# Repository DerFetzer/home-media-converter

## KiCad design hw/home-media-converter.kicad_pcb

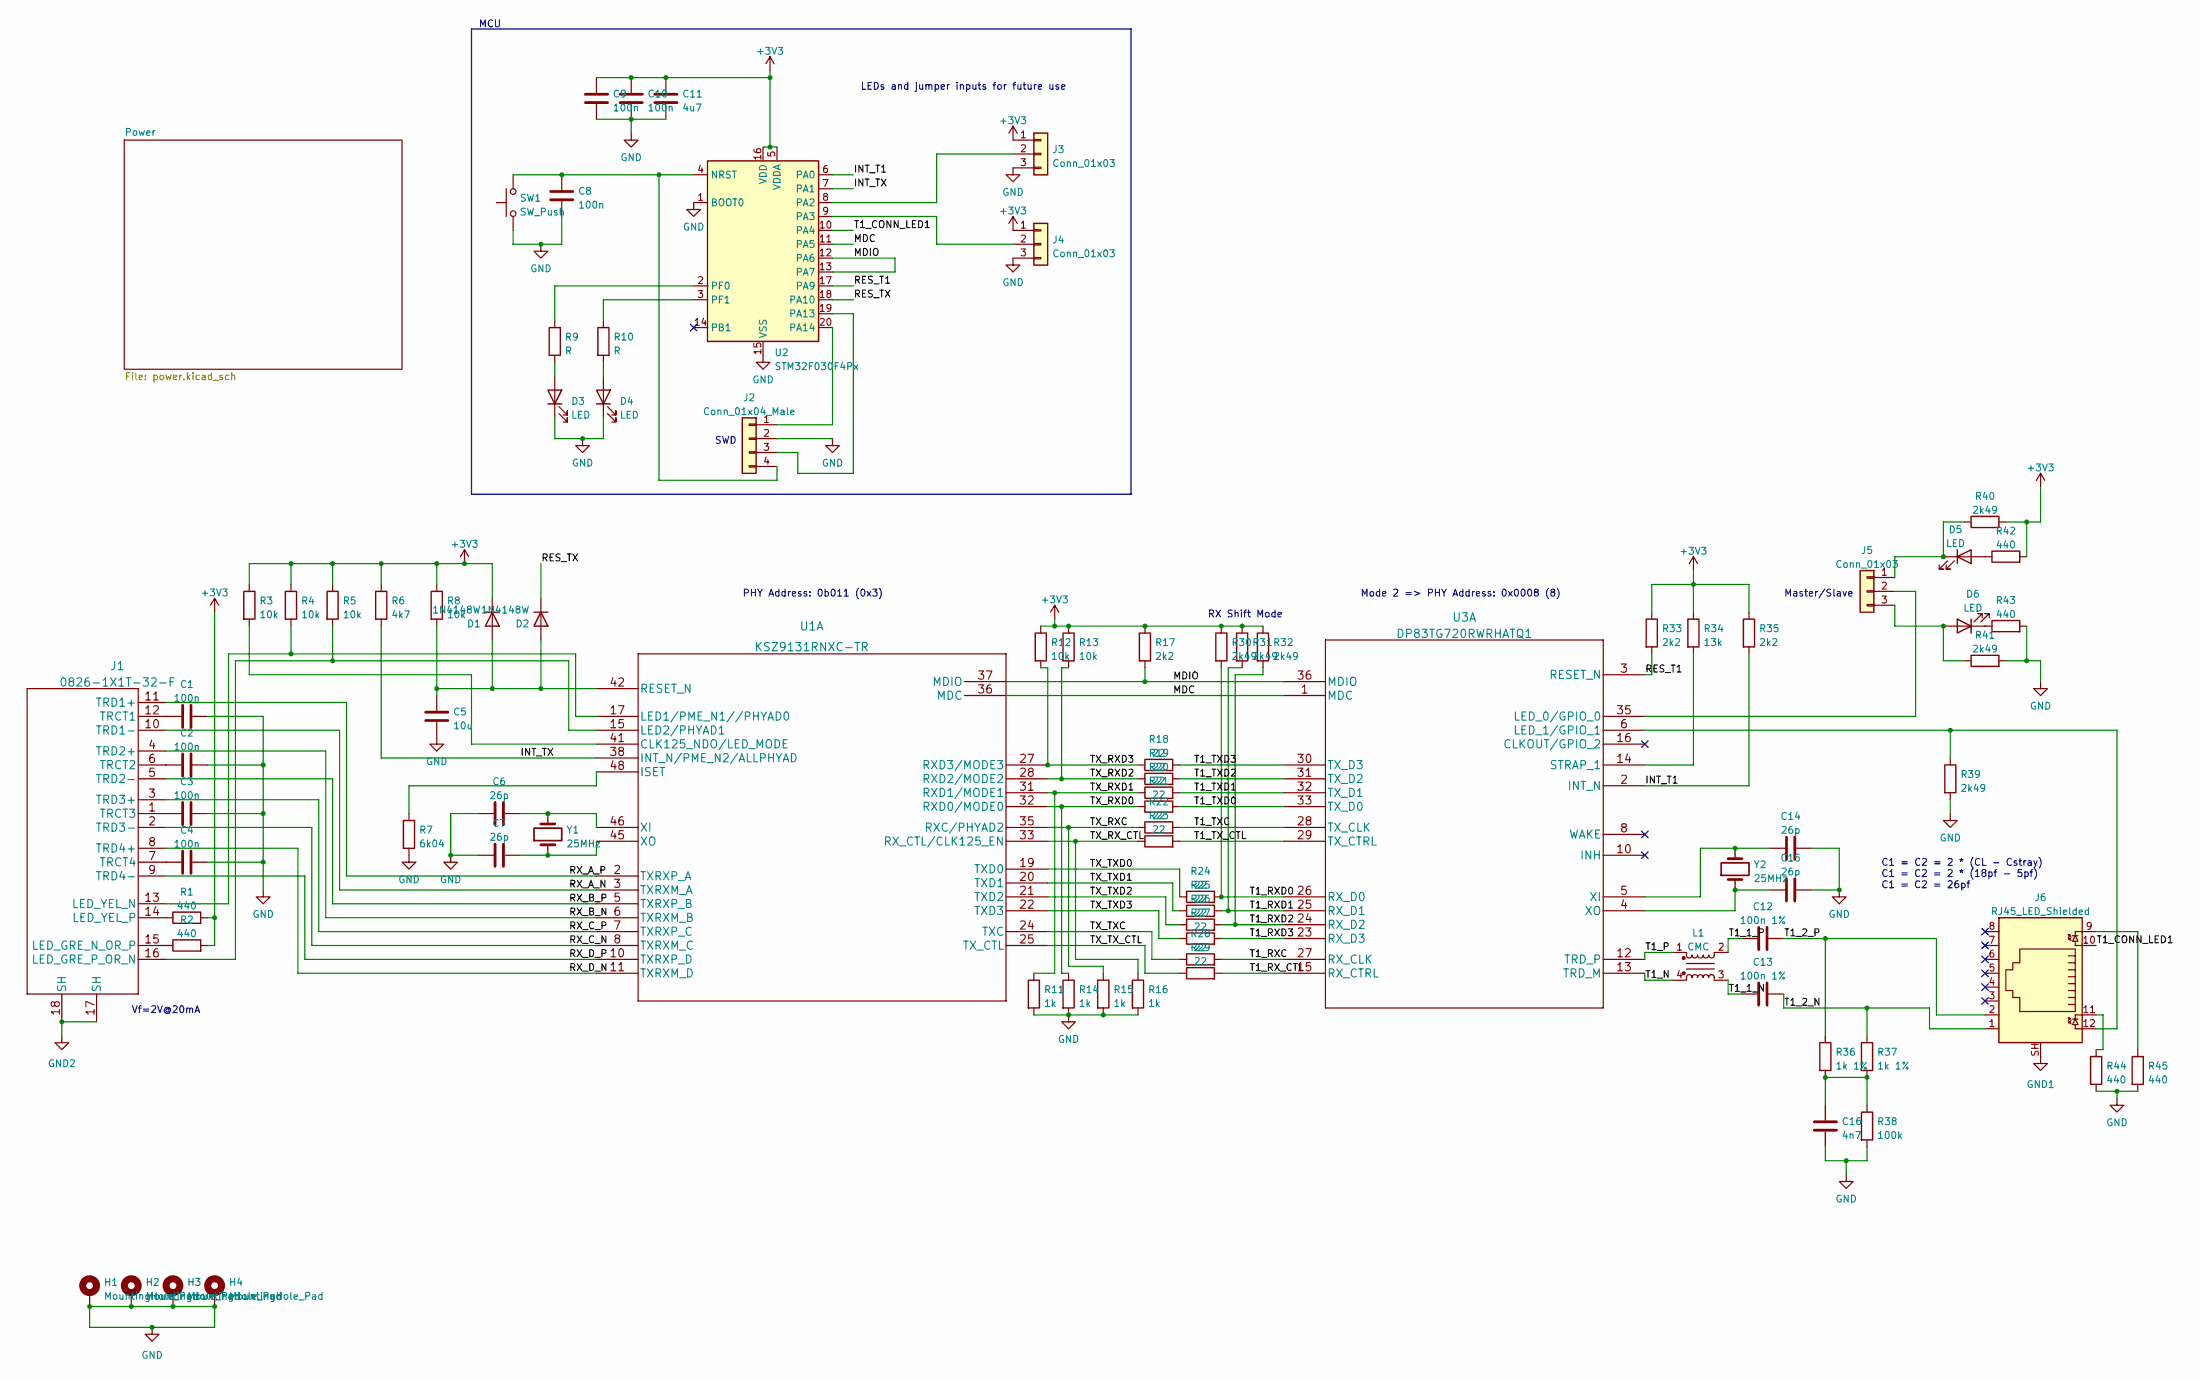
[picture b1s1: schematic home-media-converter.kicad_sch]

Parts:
C1, C2, C3, C4, C8, C9, C10: 100n; C_0402_1005Metric
C5: 10u; C_0402_1005Metric
C6, C7, C14, C15: 26p; C_0402_1005Metric
C11: 4u7; C_0402_1005Metric
C12, C13: 100n 1%; C_0402_1005Metric
C16: 4n7; C_1206_3216Metric
D1, D2: 1N4148W; D_SOD-123
D3, D4, D5, D6: LED; LED_0603_1608Metric
H1, H2, H3, H4: MountingHole_Pad; MountingHole_2.2mm_M2_DIN965_Pad_TopBottom
J1: 0826-1X1T-32-F
J2: Conn_01x04_Male; PinHeader_1x04_P2.54mm_Vertical
J3, J4, J5: Conn_01x03; PinHeader_1x03_P2.54mm_Vertical
J6: RJ45_LED_Shielded; RJ45_Amphenol_RJHSE538X
L1: CMC; DLW32MH101XK2L
R1, R2, R42, R43, R44, R45: 440; R_0402_1005Metric
R3, R4, R5, R8, R12, R13: 10k; R_0402_1005Metric
R6: 4k7; R_0402_1005Metric
R7: 6k04; R_0402_1005Metric
R9, R10: R; R_0402_1005Metric
R11, R14, R15, R16: 1k; R_0402_1005Metric
R17, R33, R35: 2k2; R_0402_1005Metric
R18, R19, R20, R21, R22, R23, R24, R25, R26, R27, R28, R29: 22; R_0402_1005Metric
R30, R31, R32, R39, R40, R41: 2k49; R_0402_1005Metric
R34: 13k; R_0402_1005Metric
R36, R37: 1k 1%; R_1206_3216Metric
R38: 100k; R_0805_2012Metric
SW1: SW_Push; SW_Push_1P1T_NO_CK_KMR2
U1: KSZ9131RNXC-TR
U2: STM32F030F4Px; TSSOP-20_4.4x6.5mm_P0.65mm
U3: DP83TG720RWRHATQ1
Y1, Y2: 25MHz; Crystal_SMD_5032-2Pin_5.0x3.2mm

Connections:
+3V3: C9.1, C10.1, C11.1, D1.1 (K), J3.1, J4.1, R1.2, R2.2, R3.1, R4.1, R5.1, R6.1, R8.1, R12.1, R13.1, R17.1, R30.1, R31.1, R32.1, R33.1, R34.1, R35.1, R40.2, R42.2, U2.5 (VDDA), U2.16 (VDD); also elsewhere on the board
/INT_T1: R35.2, U2.6 (PA0), U3.2 (INT_N)
/INT_TX: R6.2, U1.38 (INT_N/PME_N2/ALLPHYAD), U2.7 (PA1)
/MDC: U1.36 (MDC), U2.11 (PA5), U3.1 (MDC)
/MDIO: R17.2, U1.37 (MDIO), U2.12 (PA6), U2.13 (PA7), U3.36 (MDIO)
/RES_T1: R33.2, U2.17 (PA9), U3.3 (RESET_N)
/RES_TX: D2.1 (K), U2.18 (PA10)
/RX_A_N: J1.10 (TRD1-), U1.3 (TXRXM_A); also elsewhere on the board
/RX_A_P: J1.11 (TRD1+), U1.2 (TXRXP_A); also elsewhere on the board
/RX_B_N: J1.4 (TRD2+), U1.6 (TXRXM_B); also elsewhere on the board
/RX_B_P: J1.5 (TRD2-), U1.5 (TXRXP_B); also elsewhere on the board
/RX_C_N: J1.2 (TRD3-), U1.8 (TXRXM_C); also elsewhere on the board
/RX_C_P: J1.3 (TRD3+), U1.7 (TXRXP_C); also elsewhere on the board
/RX_D_N: J1.8 (TRD4+), U1.11 (TXRXM_D); also elsewhere on the board
/RX_D_P: J1.9 (TRD4-), U1.10 (TXRXP_D); also elsewhere on the board
/T1_1_N: C13.1, L1.3
/T1_1_P: C12.1, L1.2
/T1_2_N: C13.2, J6.1, R37.1
/T1_2_P: C12.2, J6.2, R36.1
/T1_CONN_LED1: J6.10, U2.10 (PA4)
/T1_N: L1.4, U3.13 (TRD_M)
/T1_P: L1.1, U3.12 (TRD_P)
/T1_RXC: R28.2, U3.27 (RX_CLK)
/T1_RXD0: R24.2, R30.2, U3.26 (RX_D0)
/T1_RXD1: R25.2, R31.2, U3.25 (RX_D1)
/T1_RXD2: R26.2, R32.2, U3.24 (RX_D2)
/T1_RXD3: R27.2, U3.23 (RX_D3)
/T1_RX_CTL: R29.2, U3.15 (RX_CTRL)
/T1_TXC: R22.2, U3.28 (TX_CLK)
/T1_TXD0: R21.2, U3.33 (TX_D0)
/T1_TXD1: R20.2, U3.32 (TX_D1)
/T1_TXD2: R19.2, U3.31 (TX_D2)
/T1_TXD3: R18.2, U3.30 (TX_D3)
/T1_TX_CTL: R23.2, U3.29 (TX_CTRL)
/TX_RXC: R15.1, R22.1, U1.35 (RXC/PHYAD2)
/TX_RXD0: R14.1, R21.1, U1.32 (RXD0/MODE0)
/TX_RXD1: R11.1, R20.1, U1.31 (RXD1/MODE1)
/TX_RXD2: R13.2, R19.1, U1.28 (RXD2/MODE2)
/TX_RXD3: R12.2, R18.1, U1.27 (RXD3/MODE3)
/TX_RX_CTL: R16.1, R23.1, U1.33 (RX_CTL/CLK125_EN)
/TX_TXC: R28.1, U1.24 (TXC)
/TX_TXD0: R24.1, U1.19 (TXD0)
/TX_TXD1: R25.1, U1.20 (TXD1)
/TX_TXD2: R26.1, U1.21 (TXD2)
/TX_TXD3: R27.1, U1.22 (TXD3)
/TX_TX_CTL: R29.1, U1.25 (TX_CTL)
GND: C1.2, C2.2, C3.2, C4.2, C5.2, C6.1, C7.1, C8.2, C9.2, C10.2, C11.2, C14.2, C15.2, C16.2, D3.1 (K), D4.1 (K), H1.1, H2.1, H3.1, H4.1, J2.2, J3.3, J4.3, R7.2, R11.2, R14.2, R15.2, R16.2, R38.2, R39.2, R41.2, R43.2, R44.2, R45.2, SW1.1, U2.1 (BOOT0), U2.15 (VSS); also elsewhere on the board
GND1: J6.SH
unnamed: C16.1, R36.2, R37.2, R38.1
unnamed: C5.1, D1.2 (A), D2.2 (A), R8.2, U1.42 (RESET_N)
unnamed: D3.2 (A), R9.2
unnamed: D4.2 (A), R10.2
unnamed: D5.2 (A), R42.1
unnamed: D5.1 (K), J5.1, R40.1
unnamed: D6.2 (A), J5.3, R41.1
unnamed: D6.1 (K), R43.1
unnamed 66: J1.15 (LED_GRE_N_OR_P), R2.1; also elsewhere on the board
unnamed 67: J1.16 (LED_GRE_P_OR_N), R5.2, U1.15 (LED2/PHYAD1); also elsewhere on the board
unnamed 68: J1.13 (LED_YEL_N), R4.2, U1.17 (LED1/PME_N1//PHYAD0); also elsewhere on the board
unnamed 69: J1.14 (LED_YEL_P), R1.1; also elsewhere on the board
unnamed: J1.17 (SH), J1.18 (SH)
unnamed 71: C1.1, J1.12 (TRCT1); also elsewhere on the board
unnamed 72: C2.1, J1.6 (TRCT2); also elsewhere on the board
unnamed 73: C3.1, J1.1 (TRCT3); also elsewhere on the board
unnamed 74: C4.1, J1.7 (TRCT4); also elsewhere on the board
unnamed: J2.1, U2.20 (PA14)
unnamed: J2.3, U2.19 (PA13)
unnamed: C8.1, J2.4, SW1.2, U2.4 (NRST)
unnamed: J3.2, U2.8 (PA2)
unnamed: J4.2, U2.9 (PA3)
unnamed: J5.2, U3.35 (LED_0/GPIO_0)
unnamed: J6.9, R45.1
unnamed: J6.11, R44.1
unnamed: R3.2, U1.41 (CLK125_NDO/LED_MODE)
unnamed: R7.1, U1.48 (ISET)
unnamed: C6.2, U1.46 (XI), Y1.2
unnamed: C7.2, U1.45 (XO), Y1.1
unnamed: R9.1, U2.2 (PF0)
unnamed: R10.1, U2.3 (PF1)
unnamed: J6.12, R39.1, U3.6 (LED_1/GPIO_1)
unnamed: R34.2, U3.14 (STRAP_1)
unnamed: C14.1, U3.5 (XI), Y2.2
unnamed: C15.1, U3.4 (XO), Y2.1

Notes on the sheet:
Vf=2V@20mA
LEDs and jumper inputs for future use
Mode 2 => PHY Address: 0x0008 (8)
C1 = C2 = 2 * (CL - Cstray) C1 = C2 = 2 * (18pf - 5pf) C1 = C2 = 26pf
SWD
RX Shift Mode
PHY Address: 0b011 (0x3)
MCU
Master/Slave

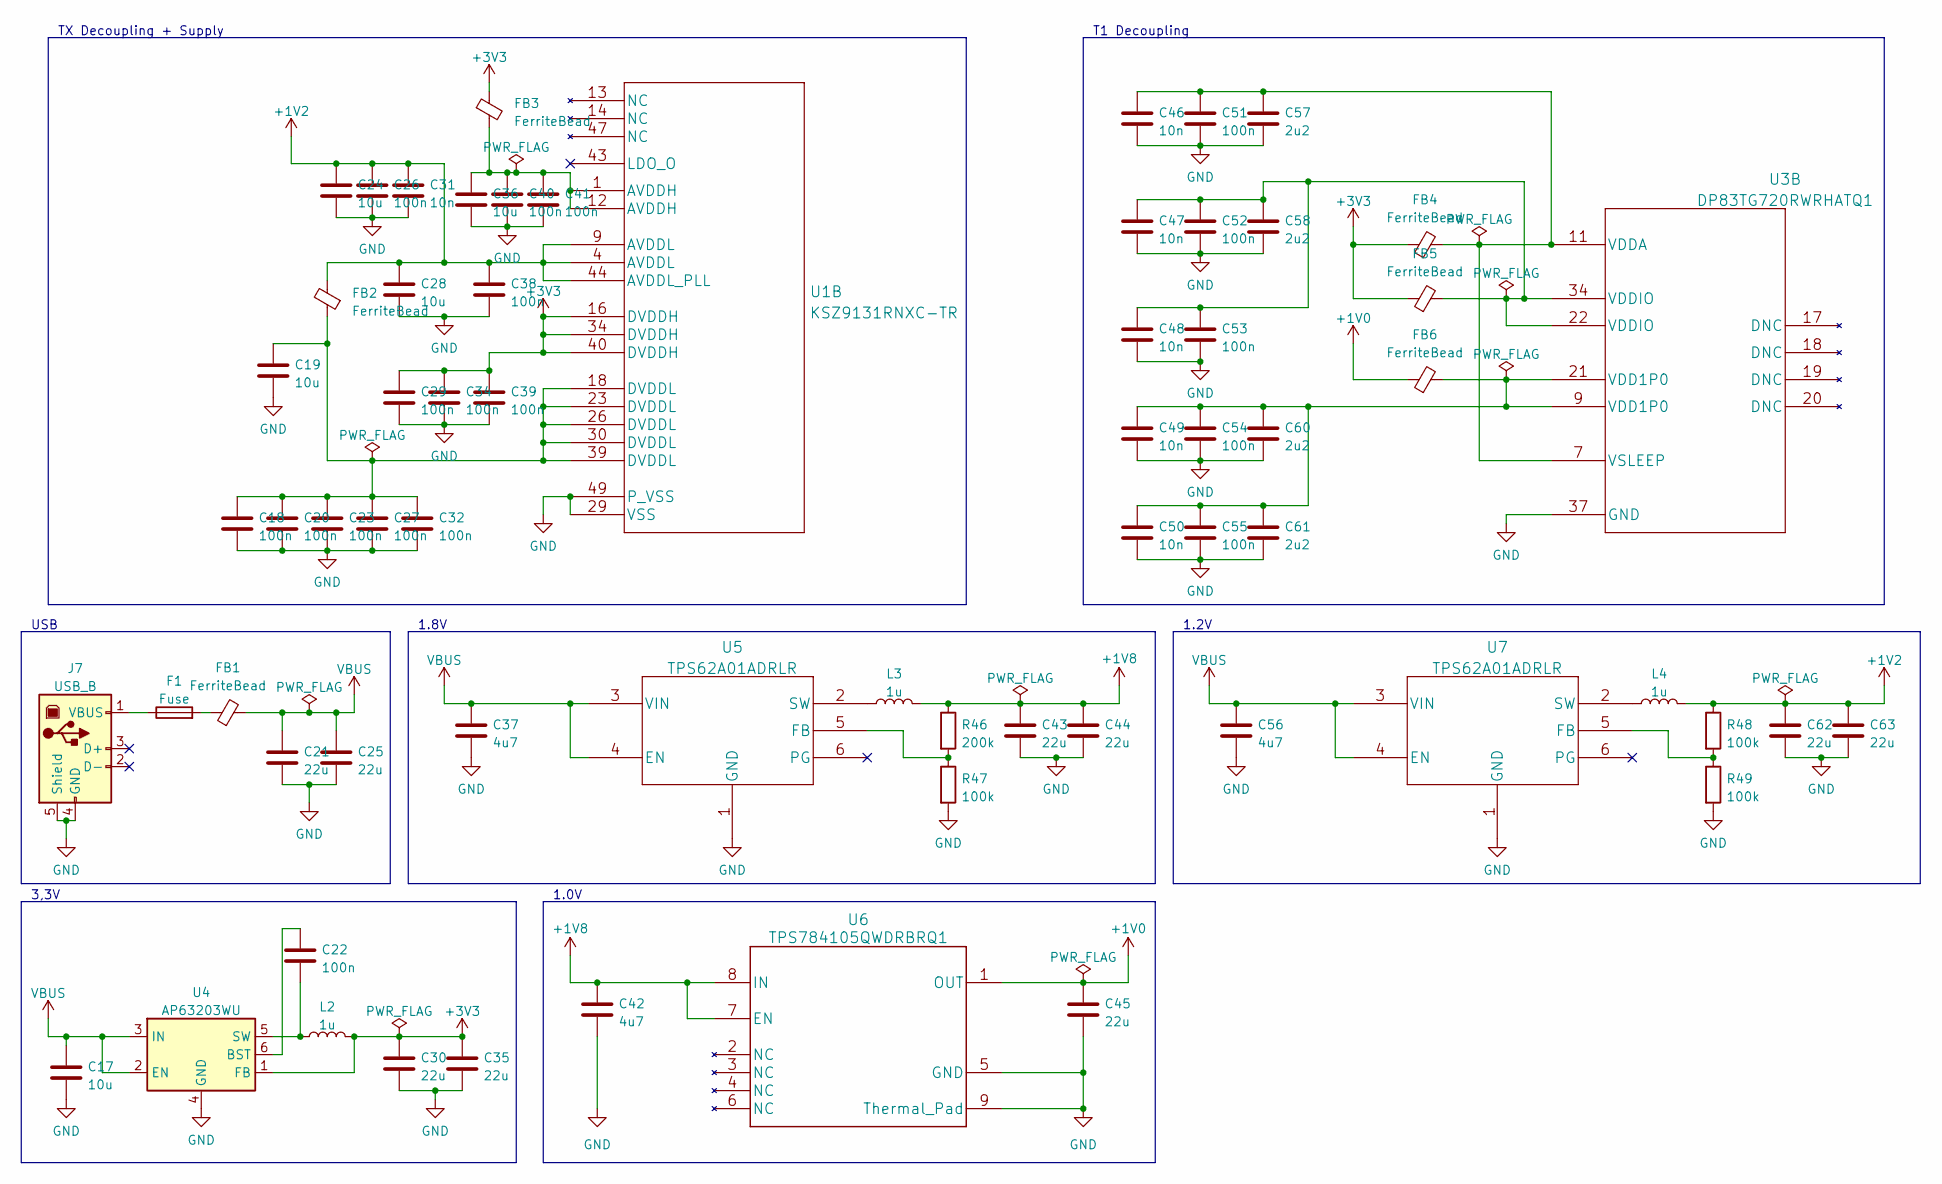
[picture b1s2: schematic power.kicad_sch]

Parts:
C17, C19, C24, C28, C36: 10u; C_0402_1005Metric
C18, C20, C22, C23, C26, C27, C29, C32, C34, C38, C39, C40, C41, C51, C52, C53, C54, C55: 100n; C_0402_1005Metric
C21, C25, C30, C35, C43, C44, C45, C62, C63: 22u; C_0603_1608Metric
C31, C46, C47, C48, C49, C50: 10n; C_0402_1005Metric
C37, C42, C56: 4u7; C_0402_1005Metric
C57, C58, C60, C61: 2u2; C_0402_1005Metric
F1: Fuse; Fuse_0603_1608Metric
FB1, FB2, FB3, FB4, FB5, FB6: FerriteBead; L_0603_1608Metric
J7: USB_B; USB_Micro-B_Wuerth_629105150521
L2, L3, L4: 1u; L_1008_2520Metric
R46: 200k; R_0402_1005Metric
R47, R48, R49: 100k; R_0402_1005Metric
U1: KSZ9131RNXC-TR
U3: DP83TG720RWRHATQ1
U4: AP63203WU; TSOT-23-6
U5, U7: TPS62A01ADRLR
U6: TPS784105QWDRBRQ1

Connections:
+1V0: C45.1, FB6.1, U6.1 (OUT)
+1V2: C24.1, C26.1, C28.1, C31.1, C38.1, C62.1, C63.1, FB2.2, L4.2, R48.1, U1.4 (AVDDL), U1.9 (AVDDL), U1.44 (AVDDL_PLL)
+1V8: C42.1, C43.1, C44.1, L3.2, R46.1, U6.7 (EN), U6.8 (IN)
+3V3: C29.1, C30.1, C34.1, C35.1, C39.1, FB3.1, FB4.1, FB5.1, L2.2, U1.16 (DVDDH), U1.34 (DVDDH), U1.40 (DVDDH), U4.1 (FB); also elsewhere on the board
GND: C17.2, C18.2, C19.2, C20.2, C21.2, C23.2, C24.2, C25.2, C26.2, C27.2, C28.2, C29.2, C30.2, C31.2, C32.2, C34.2, C35.2, C36.2, C37.2, C38.2, C39.2, C40.2, C41.2, C42.2, C43.2, C44.2, C45.2, C46.2, C47.2, C48.2, C49.2, C50.2, C51.2, C52.2, C53.2, C54.2, C55.2, C56.2, C57.2, C58.2, C60.2, C61.2, C62.2, C63.2, J7.4 (GND), J7.5 (Shield), R47.2, R49.2, U1.29 (VSS), U1.49 (P_VSS), U3.37 (GND), U4.4 (GND), U5.1 (GND), U6.5 (GND), U6.9 (Thermal_Pad), U7.1 (GND); also elsewhere on the board
unnamed: C18.1, C19.1, C20.1, C23.1, C27.1, C32.1, FB2.1, U1.18 (DVDDL), U1.23 (DVDDL), U1.26 (DVDDL), U1.30 (DVDDL), U1.39 (DVDDL)
unnamed: C36.1, C40.1, C41.1, FB3.2, U1.1 (AVDDH), U1.12 (AVDDH)
unnamed: C46.1, C51.1, C57.1, FB4.2, U3.7 (VSLEEP), U3.11 (VDDA)
unnamed: C47.1, C48.1, C52.1, C53.1, C58.1, FB5.2, U3.22 (VDDIO), U3.34 (VDDIO)
unnamed: C49.1, C50.1, C54.1, C55.1, C60.1, C61.1, FB6.2, U3.9 (VDD1P0), U3.21 (VDD1P0)
unnamed: F1.2, FB1.1
unnamed: F1.1, J7.1 (VBUS)
unnamed: C22.1, U4.6 (BST)
unnamed: C22.2, L2.1, U4.5 (SW)
unnamed: R46.2, R47.1, U5.5 (FB)
unnamed: L3.1, U5.2 (SW)
unnamed: R48.2, R49.1, U7.5 (FB)
unnamed: L4.1, U7.2 (SW)
VBUS: C17.1, C21.1, C25.1, C37.1, C56.1, FB1.2, U4.2 (EN), U4.3 (IN), U5.3 (VIN), U5.4 (EN), U7.3 (VIN), U7.4 (EN)

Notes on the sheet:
USB
TX Decoupling + Supply
1.0V
1.2V
3,3V
1.8V
T1 Decoupling

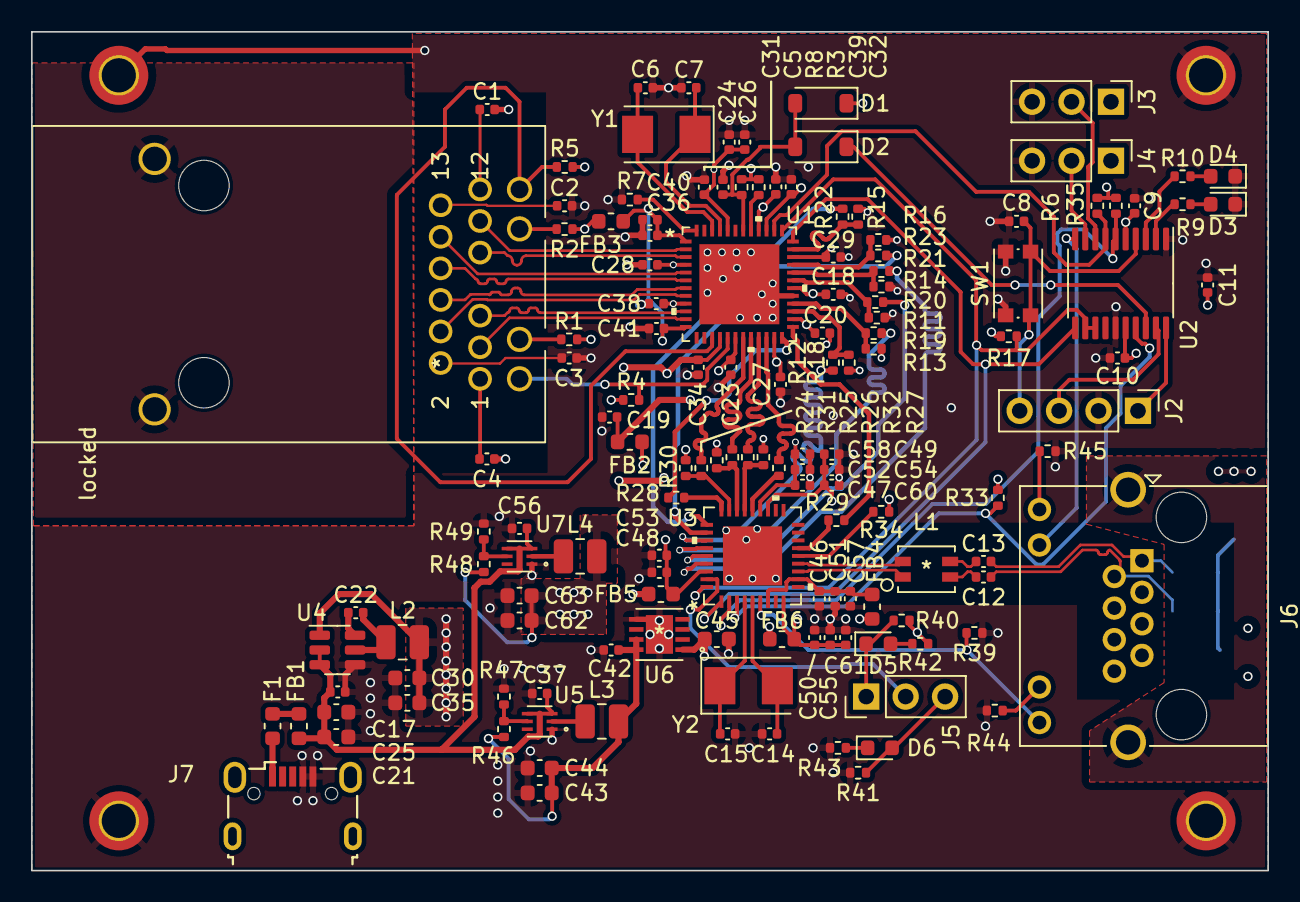
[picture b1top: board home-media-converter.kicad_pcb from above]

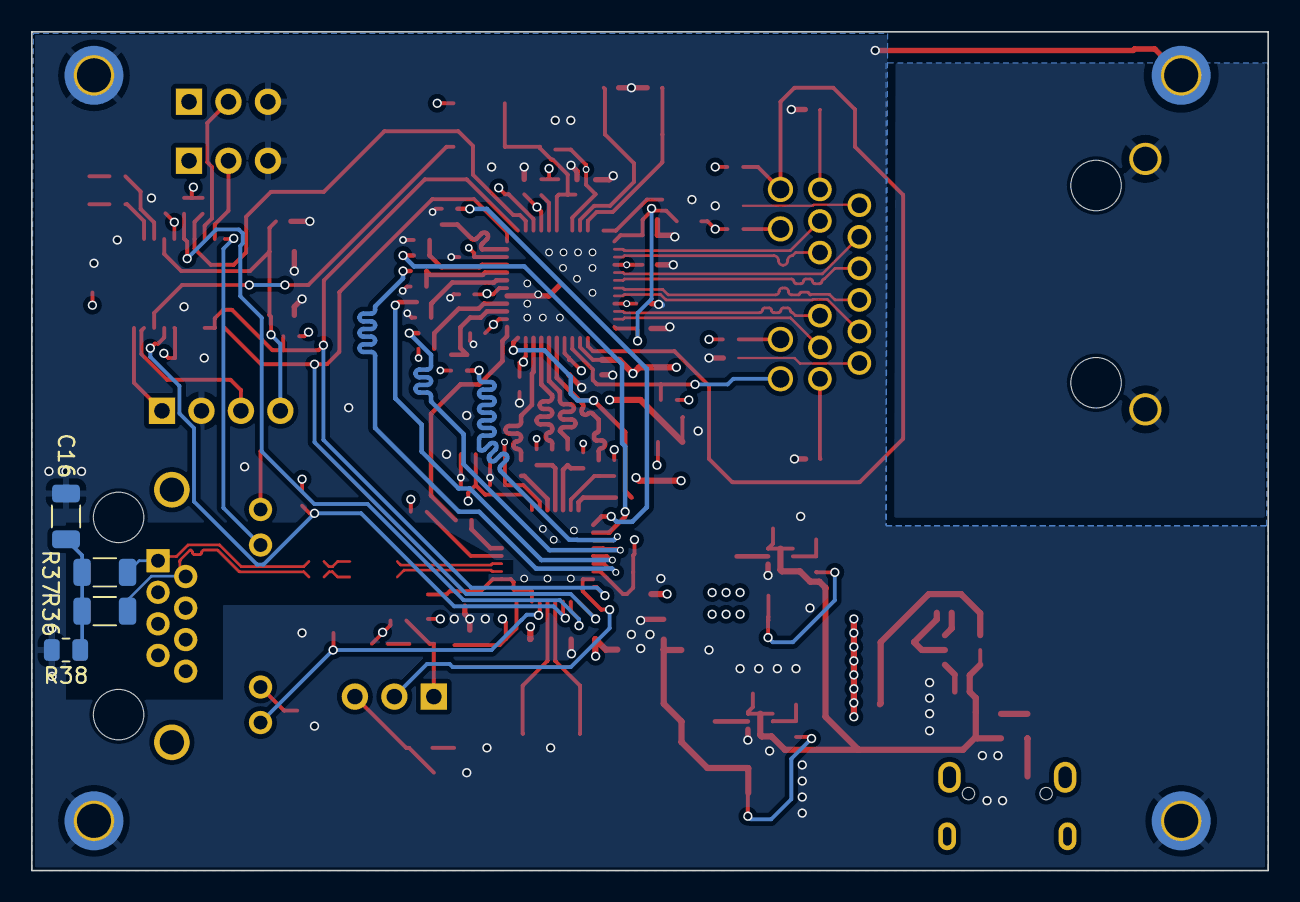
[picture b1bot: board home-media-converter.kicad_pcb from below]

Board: 4 copper layers, 79.6 x 54.0 mm, 148 parts (4 on the bottom side), 99 nets.

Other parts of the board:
locked: 0826-1X1T-32-F

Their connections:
/RX_A_N: locked.10 (TRD1-); also elsewhere on the board
/RX_A_P: locked.11 (TRD1+); also elsewhere on the board
/RX_B_N: locked.4 (TRD2+); also elsewhere on the board
/RX_B_P: locked.5 (TRD2-); also elsewhere on the board
/RX_C_N: locked.2 (TRD3-); also elsewhere on the board
/RX_C_P: locked.3 (TRD3+); also elsewhere on the board
/RX_D_N: locked.8 (TRD4+); also elsewhere on the board
/RX_D_P: locked.9 (TRD4-); also elsewhere on the board
GND2: locked.17 (SH), locked.18 (SH)
unnamed 66: locked.15 (LED_GRE_N_OR_P); also elsewhere on the board
unnamed 67: locked.16 (LED_GRE_P_OR_N); also elsewhere on the board
unnamed 68: locked.13 (LED_YEL_N); also elsewhere on the board
unnamed 69: locked.14 (LED_YEL_P); also elsewhere on the board
unnamed 71: locked.12 (TRCT1); also elsewhere on the board
unnamed 72: locked.6 (TRCT2); also elsewhere on the board
unnamed 73: locked.1 (TRCT3); also elsewhere on the board
unnamed 74: locked.7 (TRCT4); also elsewhere on the board

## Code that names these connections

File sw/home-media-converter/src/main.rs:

#![no_main]
#![no_std]

use home_media_converter as _;
use stm32f0xx_hal::pac::Peripherals; // global logger + panicking-behavior + memory layout
use stm32f0xx_hal::prelude::*;

use home_media_converter::smi::{Smi, T1Registers};

#[cortex_m_rt::entry]
fn main() -> ! {
    defmt::println!("Hello, world!");
    let mut dp = Peripherals::take().unwrap();
    let mut rcc = dp.RCC.configure().sysclk(8.mhz()).freeze(&mut dp.FLASH);

    let gpioa = dp.GPIOA.split(&mut rcc);
    let gpiof = dp.GPIOF.split(&mut rcc);

    let (jumper3, mut led_t1_conn, mdc, mdio) = cortex_m::interrupt::free(move |cs| {
        let _int_t1 = gpioa.pa0;
        let _int_tx = gpioa.pa1;

        let jumper3 = gpioa.pa2.into_pull_down_input(cs);
        let _jumper4 = gpioa.pa3.into_pull_down_input(cs);

        let _led3 = gpiof.pf0.into_push_pull_output(cs);
        let _led4 = gpiof.pf1.into_push_pull_output(cs);
        let led_t1_conn = gpioa.pa4.into_push_pull_output(cs);

        let mdc = gpioa.pa5.into_push_pull_output(cs);
        let mut mdio = gpioa.pa7.into_open_drain_output(cs);
        mdio.set_high().unwrap();

        (jumper3, led_t1_conn, mdc, mdio)
    });

    let mut sdi = Smi::new(mdc, mdio);
    loop {
        if jumper3.is_high().unwrap() {
            led_t1_conn.set_high().unwrap();
            let worst_sqi = (sdi.read_extended(8, T1Registers::SqiReq1 as u16) >> 5) & 0b111;
            defmt::println!("Worst SQI: {}", worst_sqi);
            for _ in 0..(7 - worst_sqi) {
                led_t1_conn.set_low().unwrap();
                cortex_m::asm::delay(700_000);
                led_t1_conn.set_high().unwrap();
                cortex_m::asm::delay(700_000);
            }
        } else {
            led_t1_conn.set_low().unwrap();
        }
        cortex_m::asm::delay(15_000_000);
    }
}

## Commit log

2023-03-29 Initial PCB design
2023-03-30 Bigger components on MDI
2023-03-30 Add production files
2023-03-30 Plot params
2023-04-05 Set missing part values, create BOM
2023-04-21 Fix MagJack LED polarity
2023-04-22 Add simple firmware to show SQI
2023-04-23 Slower blinking of SQI LED
2023-04-23 Move PCB to subdirectory
2023-04-26 Add housing
2023-05-08 Add description to silkscreen
2023-05-08 Modify gitignore, remove production files as they are not automatically updated
2023-05-08 Add more registers, write extended registers, add binary to generate test data
2023-05-08 Fix missing part numbers and BOM
2023-05-08 Modify BOM

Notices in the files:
parts and their libraries:
Copyright 2021 Accelerated Designs. All rights reserved.
